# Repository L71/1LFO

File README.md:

1LFO
====

Simple Eurorack LFO with triangle wave outputs. 

V2 replaces inverted triangle output with square wave output and adds a frequency range switch.
Both versions have been built and works well.

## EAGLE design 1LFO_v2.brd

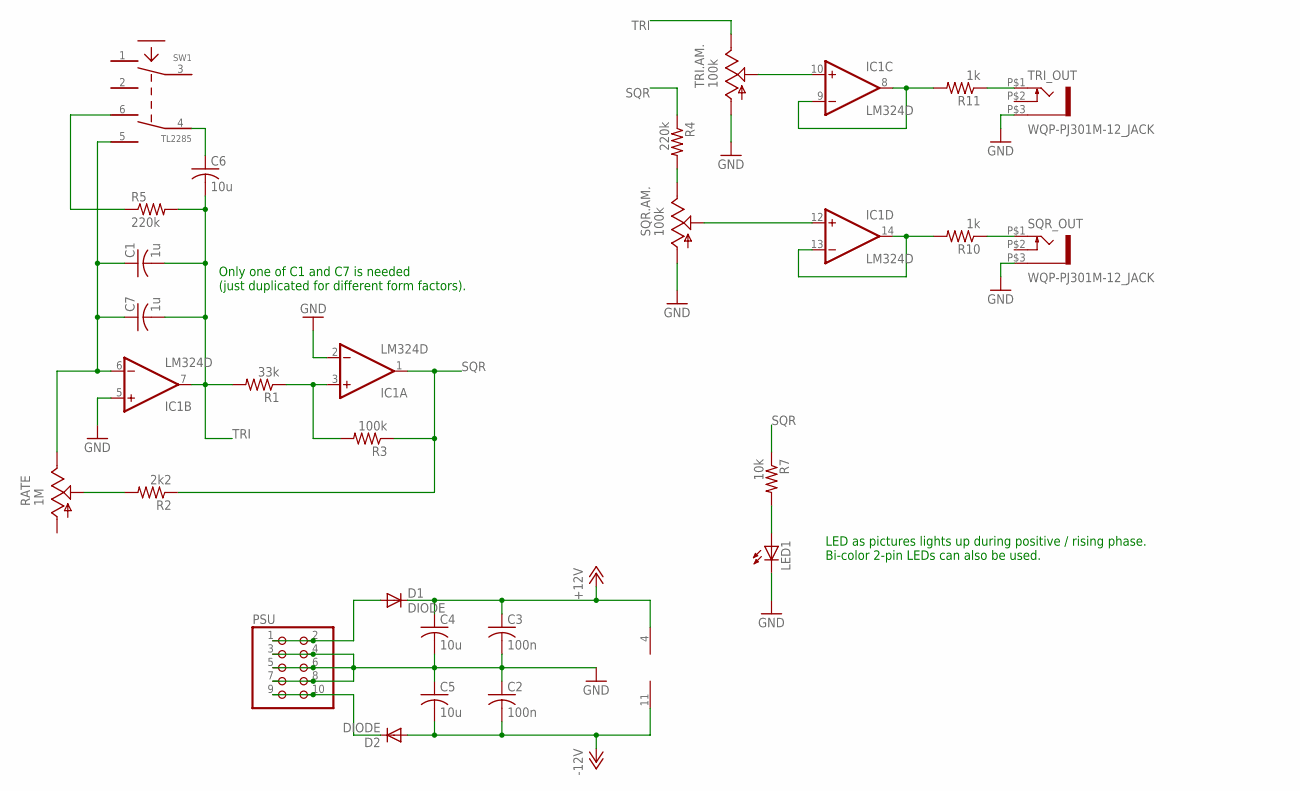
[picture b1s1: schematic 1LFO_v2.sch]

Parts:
C1: 1u; C1206K
C2, C3: 100n; C0603K
C4, C5, C6: 10u; C1206K
C7: 1u; C0603K
D1, D2: DIODE; DO214AA
IC1: LM324D; SO14
LED1: LED5MM
PSU: PINHD-2X5; 2X05
R1: 33k; R0603
R2: 2k2; R0603
R3: 100k; R0603
R4, R5: 220k; R0603
R7: 10k; R0603
R10, R11: 1k; R0603
RATE: 1M; ALPS_POT_VERTICAL
SQR.AM.: 100k; ALPS_POT_VERTICAL
SQR_OUT: WQP-PJ301M-12_JACK
SW1: TL2285; TL2285_PCB
TRI.AM.: 100k; ALPS_POT_VERTICAL
TRI_OUT: WQP-PJ301M-12_JACK

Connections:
+12V: C3.1, C4.1, D1.C, IC1.4 (V+)
-12V: C2.2, C5.2, D2.A, IC1.11 (V-)
GND: C2.1, C3.2, C4.2, C5.1, IC1.2 (-IN), IC1.5 (+IN), LED1.K (C), PSU.3, PSU.4, PSU.5, PSU.6, PSU.7, PSU.8, SQR.AM..P$3 (A), SQR_OUT.P$3 (1), TRI.AM..P$3 (A), TRI_OUT.P$3 (1)
unnamed: C1.1, C7.1, IC1.6 (-IN), RATE.P$1 (E), SW1.5
unnamed: IC1.12 (+IN), SQR.AM..P$2 (S)
unnamed: R4.2, SQR.AM..P$1 (E)
unnamed: C6.1, SW1.4
unnamed: IC1.3 (+IN), R1.1, R3.2
unnamed: R5.1, SW1.6
unnamed: R2.2, RATE.P$2 (S)
unnamed: IC1.8 (OUT), IC1.9 (-IN), R11.2
unnamed: IC1.10 (+IN), TRI.AM..P$2 (S)
unnamed: D1.A, PSU.1, PSU.2
unnamed: D2.C, PSU.9, PSU.10
unnamed: LED1.A, R7.2
unnamed: IC1.13 (-IN), IC1.14 (OUT), R10.2
unnamed: R11.1, TRI_OUT.P$1 (2)
unnamed: R10.1, SQR_OUT.P$1 (2)
SQR: IC1.1 (OUT), R2.1, R3.1, R4.1, R7.1
TRI: C1.2, C6.2, C7.2, IC1.7 (OUT), R1.2, R5.2, TRI.AM..P$1 (E)

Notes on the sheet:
Only one of C1 and C7 is needed (just duplicated for different form factors).
LED as pictures lights up during positive / rising phase. Bi-color 2-pin LEDs can also be used.

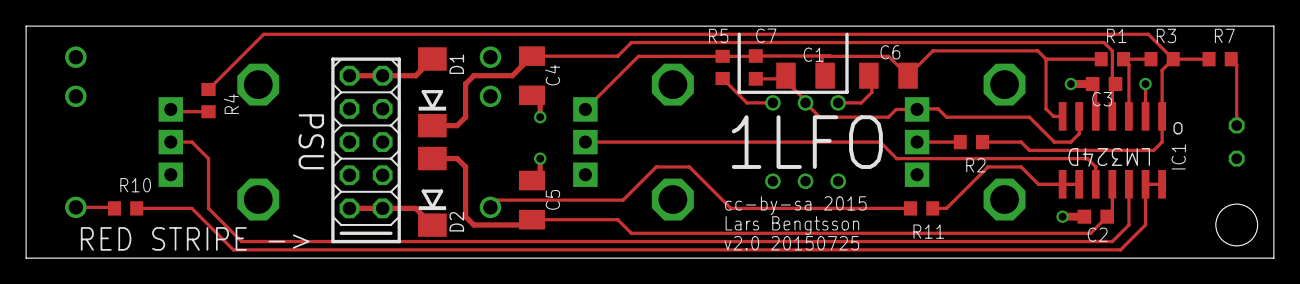
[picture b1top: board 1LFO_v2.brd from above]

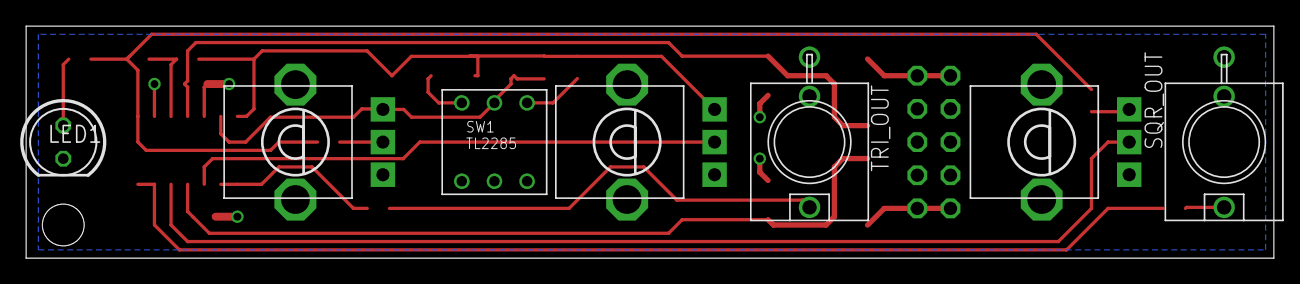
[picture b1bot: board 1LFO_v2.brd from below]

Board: 2 copper layers, 95.6 x 17.8 mm, 26 parts (7 on the bottom side), 20 nets.

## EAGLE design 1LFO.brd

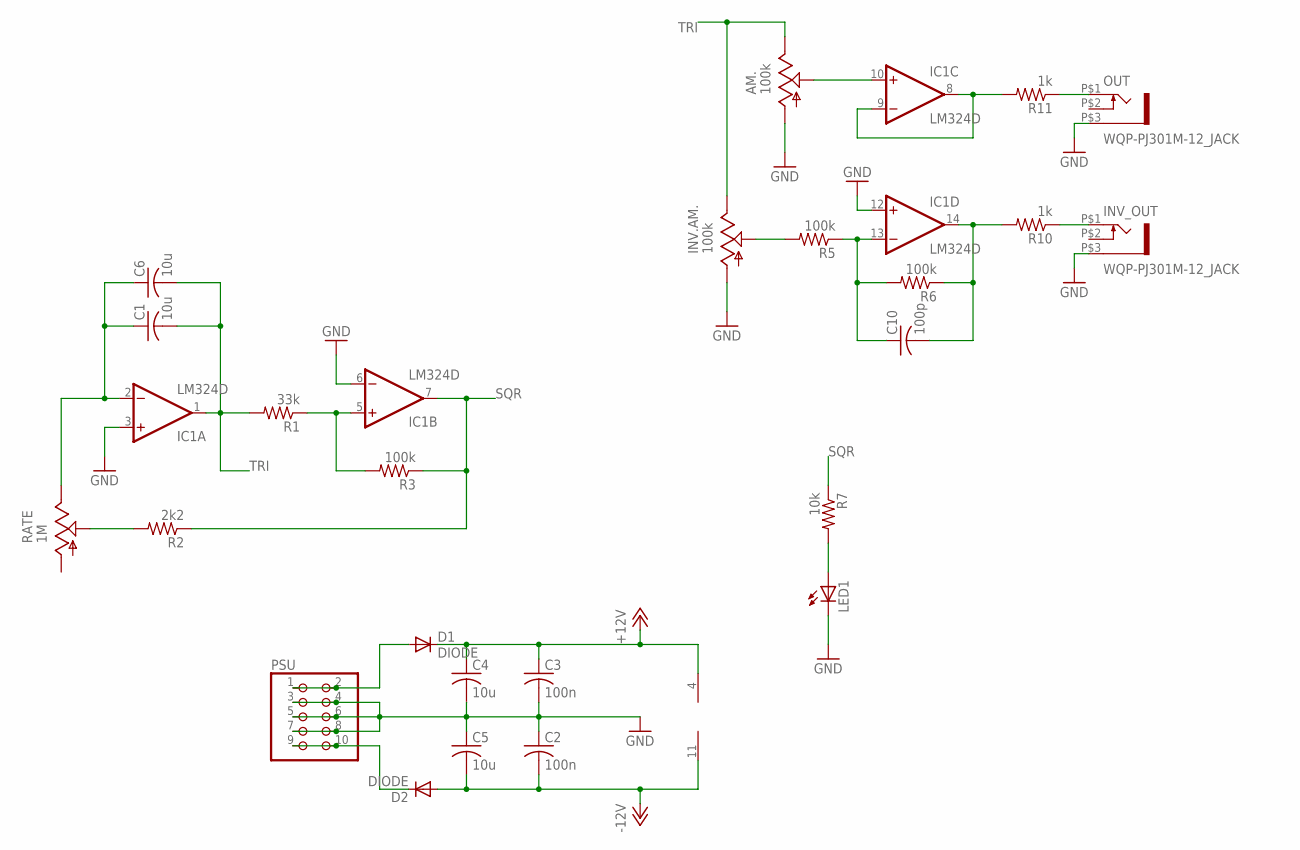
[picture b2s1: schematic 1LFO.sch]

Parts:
AM.: 100k; ALPS_POT_VERTICAL
C1, C4, C5: 10u; C1206K
C2, C3: 100n; C0603K
C6: 10u; C0603K
C10: 100p; C0603K
D1, D2: DIODE; DO214AA
IC1: LM324D; SO14
INV.AM.: 100k; ALPS_POT_VERTICAL
INV_OUT: WQP-PJ301M-12_JACK
LED1: LED3MM
OUT: WQP-PJ301M-12_JACK
PSU: PINHD-2X5; 2X05
R1: 33k; R0603
R2: 2k2; R0603
R3, R5, R6: 100k; R0603
R7: 10k; R0603
R10, R11: 1k; R0603
RATE: 1M; ALPS_POT_VERTICAL

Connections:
+12V: C3.1, C4.1, D1.C, IC1.4 (V+)
-12V: C2.2, C5.2, D2.A, IC1.11 (V-)
GND: AM..P$3 (A), C2.1, C3.2, C4.2, C5.1, IC1.3 (+IN), IC1.6 (-IN), IC1.12 (+IN), INV.AM..P$3 (A), INV_OUT.P$3 (1), LED1.K (C), OUT.P$3 (1), PSU.3, PSU.4, PSU.5, PSU.6, PSU.7, PSU.8
unnamed: C1.1, C6.1, IC1.2 (-IN), RATE.P$1 (E)
unnamed: INV.AM..P$2 (S), R5.2
unnamed: IC1.5 (+IN), R1.1, R3.2
unnamed: R2.2, RATE.P$2 (S)
unnamed: IC1.8 (OUT), IC1.9 (-IN), R11.2
unnamed: AM..P$2 (S), IC1.10 (+IN)
unnamed: D1.A, PSU.1, PSU.2
unnamed: D2.C, PSU.9, PSU.10
unnamed: C10.1, IC1.13 (-IN), R5.1, R6.2
unnamed: LED1.A, R7.2
unnamed: C10.2, IC1.14 (OUT), R6.1, R10.2
unnamed: OUT.P$1 (2), R11.1
unnamed: INV_OUT.P$1 (2), R10.1
SQR: IC1.7 (OUT), R2.1, R3.1, R7.1
TRI: AM..P$1 (E), C1.2, C6.2, IC1.1 (OUT), INV.AM..P$1 (E), R1.2

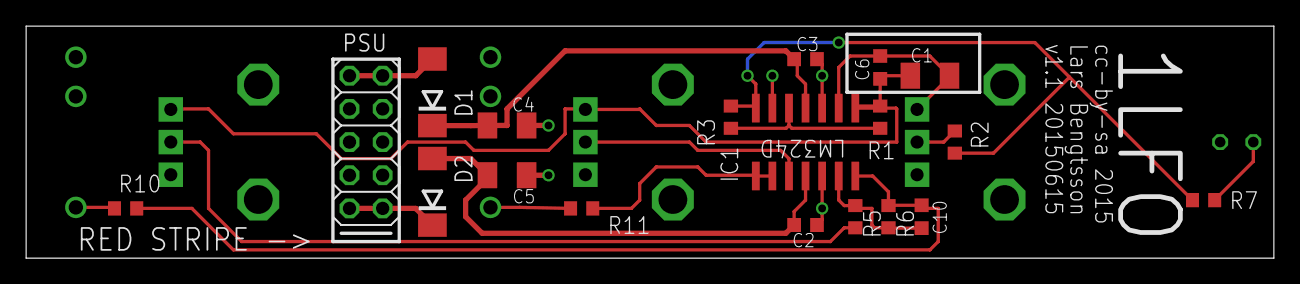
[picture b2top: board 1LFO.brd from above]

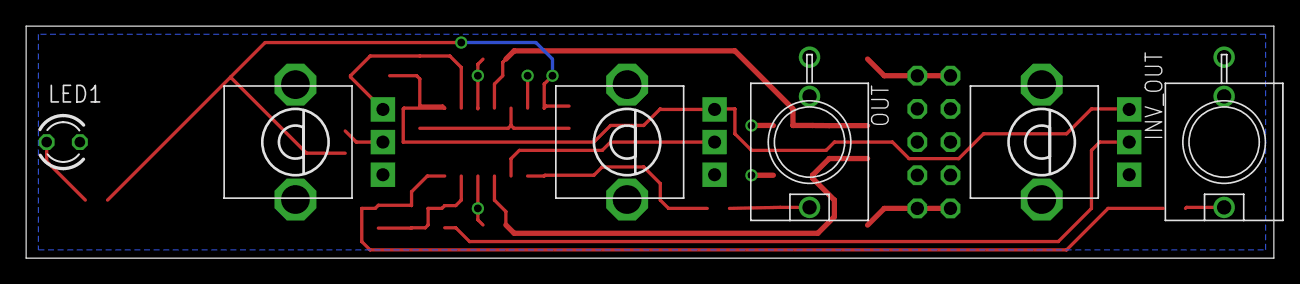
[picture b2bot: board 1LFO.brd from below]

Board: 2 copper layers, 95.6 x 17.8 mm, 25 parts (6 on the bottom side), 18 nets.

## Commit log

2015-06-06 Initial commit.
2015-06-06 added readme file.
2015-06-07 Initial panel drawing (Ponoko specs.)
2015-06-15 Use 3mm LED package (fits on board, panel still has 5mm hole).
2015-06-15 Moved LED 2.54mm up, fits panel now (originally a mistake, but panel looks fine now. Better fix board). Also, size down other end of PCB to save a few cents on manufacturing.
2015-06-15 Removed C7. Moved remaining timing caps a bit and changed value to the right one (10uF). Only one of C1 and C6 needs to be fitted. 10uF caps are easier to find in 1206 packages with higher voltage to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
2015-07-25 Initial commit of v2 with square wave output too.
2015-07-25 Added button hole.
2015-07-25 Added switch to select LFO rate range. Moved IC1 & rerouted to make room for the same.
2015-07-25 Minor routing polish :)
2015-07-25 Set lines to 0.01mm, added line between rate knob and button.
2015-07-26 Inverted square output signal art. Now phase correct with respect to triangle output.
2015-07-29 Adjusted text style to match the latest other modules.
2015-08-22 Updated readme after build.
2015-10-24 Added hole for support spacer, may be needed if weak panel is used and the rate potentiometer can't be fixed to it.
2016-01-11 Adjusted panel size and bottom hole downwards 1/40" to hopefully fit racks w 3mm screws.

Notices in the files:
1LFO.brd:
cc-by-sa 2015
